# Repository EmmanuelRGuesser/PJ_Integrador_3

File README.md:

---

# Medidor de consumo elétrico residencial com ESP32
---

Este projeto tem como objetivo realizar o projeto e implementação de um dispositivo de monitoramento do consumo energético de tomadas residenciais integrado ao Home Assistant.

Dispositivos como esse permitem aos usuários monitorar e controlar o consumo de energia, ajudando a identificar aparelhos que consomem muita energia e incentivar hábitos mais sustentáveis. Isso resulta em uma redução significativa na fatura de energia e contribui para a conservação de recursos naturais.

Com o aumento das tarifas de energia elétrica, ser capaz de identificar os maiores consumidores de energia em casa pode gerar economia substancial. Um dispositivo que fornece dados detalhados permite aos consumidores tomar decisões informadas para reduzir o consumo e, consequentemente, os custos.

## Funcionalidades:

- Integração com o Home Assistant;
- Monitoramento da tensão, corrente, potência, frequência e fator de potência;
- Visualiazação do histórico de consumo;
- Sistema de acionamento a distância;
- Sistema de proteção do dispositivo.  

## Dispositivo

O dispositivo funcionará entre as tomadas adquirindo os dados por meio do sensor PZEM-004T, abaixo temos uma representação dele:

Ele deve ser conectado a tomada para o fornecimento de energia, dentro da case possui uma fonte para alimentar o ciruito. Esse circuito é composto pelo microcontrolador(ESP32), sensor(PZEM-004t), relé de acionamento e leds para fácil identificação do funcionamento, já a interface será integrada com o Home Assistant.

Para o projeto será utilizado os seguintes componentes:
- ESP32
- PZEM-004t
- Relé
- Fonte Hi-link 5V 3W
- 2 leds
- Display LCD 20x4
- Case takachi WPL15-15-6

---
## Descrição dos componentes

### ESP32
O ESP32 é um microcontrolador de baixo custo e baixa potência, desenvolvido pela Espressif Systems. Ele integra Wi-Fi e Bluetooth, tornando-se uma escolha popular para projetos de Internet das Coisas (IoT), além disso a comunidade em torno do ESP32 é enorme, com muitos recursos, bibliotecas e tutoriais disponíveis. A Espressif, empresa desenvolvedora, também oferece um SDK robusto (ESP-IDF). 

### PZEM-004t
O PZEM-004T é um módulo que possui funcionalidades de Voltimetro, Amperímetro e Wattimetro. Os dados são transmitidos para o microcontrolador por meio de comunicação serial TTL. 

### Fonte Hi-link 5V
É um conversor step down que trabalha com uma tensão de alimentação AC-DC 127/220V para 5V, com uma potencia de 5W, o qual será suficiente para alimentar o microcontrolador e os periféricos contidos no circuito. Foi escolhido esse modelo de fonte pois é compacta, facil de encontrar no mercado e possui certificações que garantem a qualidade da tensão e corrente entregues na saída, dentro da potencia especificada.

### LEDs
O dispositivo conta com dois leds que dão um feedback do funcionamento do sistema. Um led vermelho indicará que o circuito está ligado e outro led verde indicará estado de conexão com o wifi.

---
## Home Assistant

O Home Assistant é uma plataforma de automação residencial de código aberto que permite controlar dispositivos e sistemas em sua casa de maneira centralizada e automatizada. Ele suporta uma ampla variedade de dispositivos e protocolos, facilitando a criação de cenários de automação e controle de tudo, desde luzes e termostatos até câmeras de segurança e sistemas de entretenimento.

#### Principais características do Home Assistant:
- Automação: Criação de regras de automação personalizadas com base em eventos, horários ou condições específicas.
- Integrações: Suporte a milhares de dispositivos e serviços, como Philips Hue, Google Assistant, Amazon Alexa, entre muitos outros.
- Controle Local: Embora possa ser integrado à nuvem, o Home Assistant é projetado para funcionar localmente, o que oferece maior privacidade e controle.
- Dashboard Personalizado: A plataforma oferece uma interface visual personalizável para que você possa monitorar e controlar dispositivos.

#### Integração com ESP32 no Home Assistant
O ESP32 é um microcontrolador com conectividade Wi-Fi e Bluetooth, amplamente utilizado em projetos de automação e IoT (Internet das Coisas). No contexto do Home Assistant, o ESP32 é frequentemente usado para criar dispositivos personalizados, como sensores e atuadores. A integração entre o ESP32 e o Home Assistant ocorre principalmente por meio do protocolo MQTT Moskitto.

Funcionamento da Integração:

1. Configurar a rede Wi-Fi e login do Home Assistant na pagina WEB gerada pelo ESP.
2. O Home Assistant recebe os dados por meio do protocolo MQTT Moskito.
3. Armazena os dados em forma de entidades, no bando de dados InfluxDB.
4. No banco de dados possui um dashboard o qual mostra todos os dados plotados para o gerenciamento.

---

## Funcionamento do Monitor de Energia

Para o funcionamento do dispositivo devemos conectar a rede Wi-FI, isso é feito através do aplicativo ESP BLE Provising que está disponível na Play Store e App Store, leia o [código QR do link](https://espressif.github.io/esp-jumpstart/qrcode.html?data=%7B%22ver%22:%22v1%22,%22name%22:%22Monitor%20de%20energia%22,%22pop%22:%22abcd1234%22,%22transport%22:%22ble%22%7D) ou procure por monitor de energia e use a senha “abc1234”, com isso você pode ver as redes disponíveis e fazer a conexão, caso necessário reconfigurar a rede, somente pressione o botão ao lado da entrada de alimentação por 3 segundos que seu dispositivo irá reiniciar e basta seguir os passos anteriores. 

Agora é possível acessar a página de configurações através do Web Server gerado pela ESP32, acesse [monitor-energia.local](http://monitor-energia.local/), através dela você deve configurar o serviço MQTT para realizar a comunicação de dados entre o monitor de energia e o Home Assistant, use sua conta e senha do seu perfil do HA. Você também pode configurar os alertas, visualizar o consumo acumulado, além de ligar e desligar o dispositivo conectado através da página.

O sistema de alertas funciona como uma proteção que irá atuar desligando o dispositivo conectado ao monitor, a proteção age sobre tensão mínima e tensão, corrente e potência máxima, sempre que um alerta é disparado um aviso é exibido na tela, para voltar ao funcionamento basta clicar no botão ligar. Caso você queira não utilizar os alertas, somente deixe o item com 0. 
Na página de consumo acumulado é exibido quantidade de energia consumida pelo dispositivo conectado, com isso você pode estimar o valor gasto com ele, caso você queira trocar o dispositivo monitorado ou no que for necessário, você pode zerar o contador clicando em zerar energia.

Com isso, já é possível ver na tela LCD do monitor dados como tensão, corrente, potência e energia consumida, além dos avisos do dispositivos e informaçãoes já descritas acima, isso sem a necessidade de integrar com o Home Assistant , porém para conseguir monitorar os dados ao decorrer do tempo em um gráfico, você deve seguir os passos abaixo.

---
### Instalação do Home Assistant
Como o Home Assistant funciona localmente é necessário fazer a instalação em um computador, máquina virtual ou um Raspberry Pi por exemplo. 

Para acessar o processo de instalação [click aqui](https://www.home-assistant.io/installation/).

Com o Home Assistant instalado vamos adicionar o Moskitto MQTT

---
### Guia para Adicionar MQTT Mosquitto no Home Assistant
Instalar o Add-on:

Acesse Configurações → Add-ons, Backup & Supervisor
Vá em Loja de Add-ons e instale o Mosquitto broker
Configurar o Mosquitto:

No add-on, clique em Configuração e edite conforme necessário
Se precisar de autenticação, crie usuários em Configurações → Pessoas e Acesso
Habilitar e Iniciar:

Ative Iniciar na inicialização e Assistente de Rede
Clique em Iniciar
Verificar Funcionamento:

Vá em Configurações → Dispositivos e Serviços
Adicione uma integração MQTT, com isso no menu de configurações já deve ser possível se inscrever em algum tópico para receber os pacotes via MQTT.
No momento têm-se o tópico *sensor* e os sub tópicos *voltage, current, power, energy, frequency e pf*, para ver a tensão por exemplo, deve-se se inscrever no *sensor/voltage*, como resultado você deve ver algumo semelhante a isto:

Para salvar os dados será utilizado o File editor para criar as entidades que serão atribuidas aos dados que são recebidos via mqtt.

Com o File Editor aditaremos o arquivo */homeassistant/configuration.yaml*, basta adicionar o seguinte código para criar as entidades:
```
mqtt:    
    sensor:
        - name: voltage
          state_topic: "sensor/voltage"
          unit_of_measurement: V

        - name: current
          state_topic: "sensor/current"
          unit_of_measurement: A

        - name: power
          state_topic: "sensor/power"
          unit_of_measurement: W

        - name: energy
          state_topic: "sensor/energy"
          unit_of_measurement: Wh

        - name: frequency
          state_topic: "sensor/frequency"
          unit_of_measurement: Hz
          
        - name: fp
          state_topic: "sensor/pf"
          unit_of_measurement: fp
```
Agora vamos criar o banco de dados com o InfluxDB, para armazenar os dados e os manipular.

---
### Adicionando o InfluxDB no Home Assistant
Instalar o Add-on:

Acesse Configurações → Add-ons, Backup & Supervisor
Instale o InfluxDB
Criar um Banco de Dados e Usuário:

No terminal do InfluxDB, execute:
```
CREATE DATABASE home_assistant;
CREATE USER ha_user WITH PASSWORD 'senha' WITH ALL PRIVILEGES;
```
(Opcional) Restringir permissões:
```
GRANT ALL ON home_assistant TO ha_user;
```
Configurar no Home Assistant:
Adicione no configuration.yaml:
```
influxdb:
  host: a0d7b954-influxdb
  port: 8086
  database: home_assistant
  username: ha_user
  password: senha
  max_retries: 3
  default_measurement: state
```
Reinicie o Home Assistant

Para Verificar Funcionamento:

Acesse Desenvolvedor → Ferramentas de Estado para ver os dados sendo enviados

Pronto! Agora o MQTT e o InfluxDB estão integrados ao Home Assistant. 🚀

---
### Gerar o Dashboard e os gráficos no InfluxDB
1. Acessar o InfluxDB
2. No Home Assistant, vá para Configurações → Add-ons, Backup & Supervisor
Abra o InfluxDB e clique em Abrir Web UI
3. Criar um Dashboard
No menu lateral, vá em Dashboards
Clique em + Create Dashboard
Dê um nome ao dashboard e clique em Create
4. Criar um Gráfico
No dashboard criado, clique em + Create Cell
Escolha o tipo de visualização (Linha, Barras, Gauge, etc.)
Selecione Configure Query e escolha o banco de dados home_assistant
5. Construir a Query
   
OBS: O código das query estão no arquivo [Código_dos_gráficos_influxDB.md](https://github.com/EmmanuelRGuesser/PJ_Integrador_3/blob/main/C%C3%B3digo_dos_gr%C3%A1ficos_influxDB.md)

6. Utilizando os códigos, você pode personalizar os gráficos como desejar.

---

### Teste do Monitor de Energia

Para o teste vamos monitorar o carregamento de um notebook, após realizar as configuração de conexão do monitor e do Home Assistant conforme o passo a passo acima, podemos monitorar o consumo através da tela LCD no monitor ou pelo dashboard no Home Assistant.

Como visto acima podemos monitorar os parâmetros elétricos do dispositivo conectado ao monitor. Vamos testar o sistema de proteção, como a potência consumida é entre 15W - 20 W então para provocar um alerta iremos limitar em 10W, para isso entramos no página web do monitor de energia → configurar alertas e colocamos Max Power com 10W.

Como vemos acima o monitor entra em modo proteção e desliga a carga, para voltar a funcionar é necessário ligar novamente no menu principal.

O consumo acumulado pode ser acessado pelo menu e la você poderá estimar o valor gasto pela caraga conectada, somente digite o valor pago por kWh e calcule. Caso você quiser zerar o contador nesta página também é possível fazer isto.

---

## Considerações finais

O desenvolvimento do projeto atingiu seus objetivos propostos, resultando em um dispositivo funcional capaz de monitorar o consumo elétrico de forma eficiente. A integração do hardware e software permitiu a coleta e visualização dos dados em tempo real, proporcionando um produto prático para automação residencial. Para projetos futuros, considera-se a possibilidade de utilizar um banco de dados mais robusto, um software mais avançado para a criação do dashboard e a adoção de componentes SMD para um design mais compacto, eficiente e profissional, reduzindo o tamanho da case e aprimorando a estética e usabilidade do dispositivo.

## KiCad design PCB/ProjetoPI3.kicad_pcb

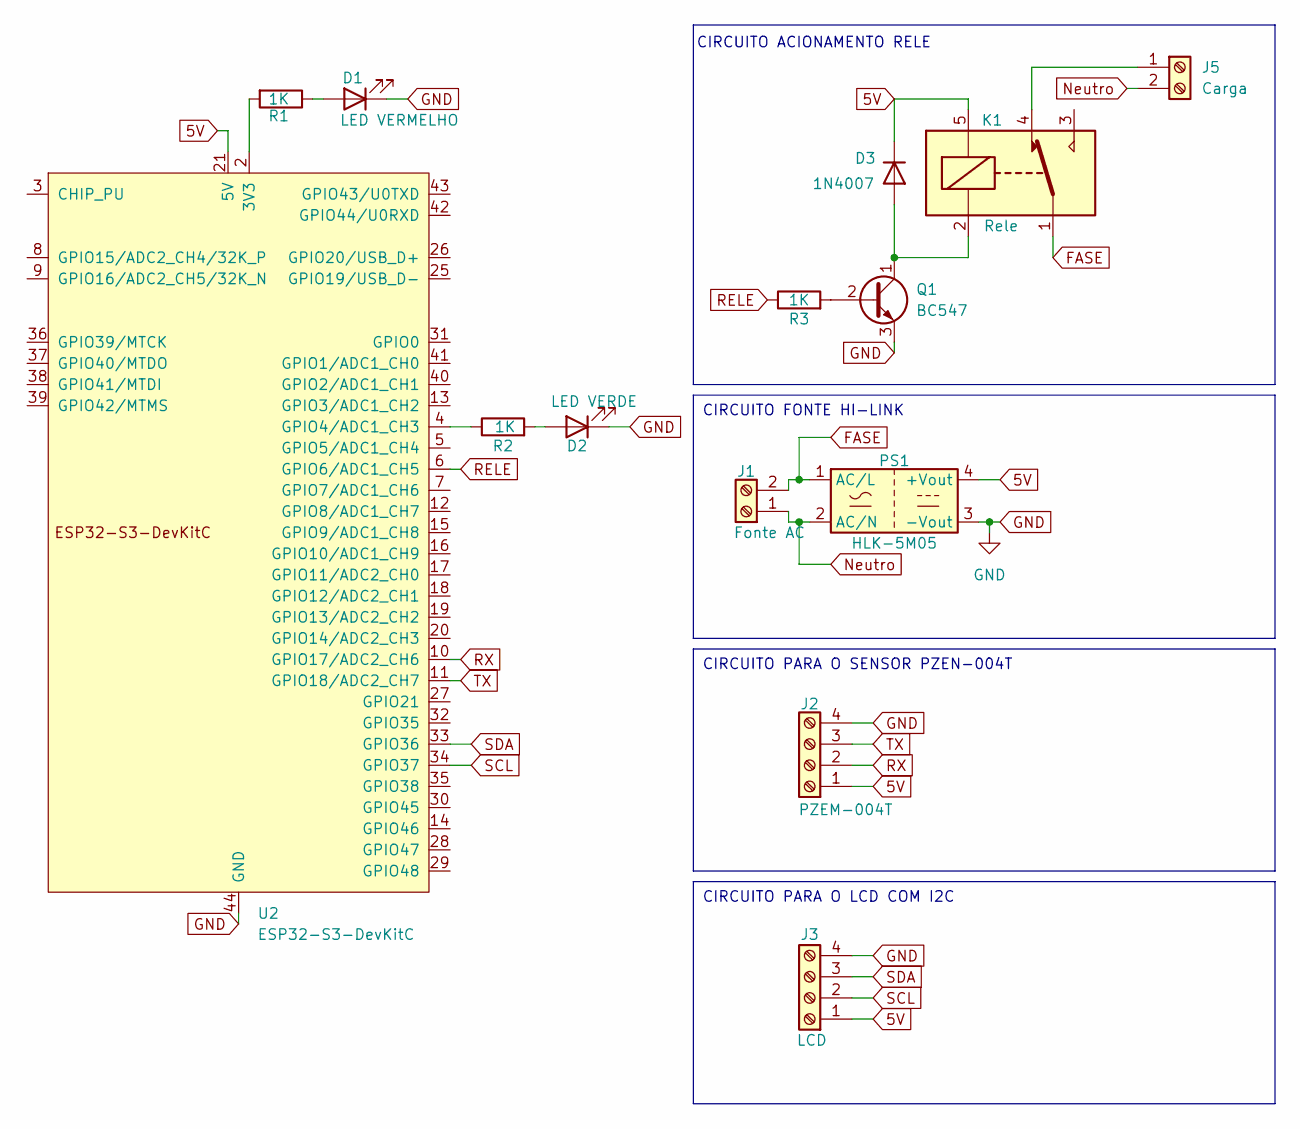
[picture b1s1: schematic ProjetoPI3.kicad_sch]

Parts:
D1: LED VERMELHO; TerminalBlock_Altech_AK300-2_P5.00mm
D2: LED VERDE; TerminalBlock_Altech_AK300-2_P5.00mm
D3: 1N4007; D_DO-41_SOD81_P10.16mm_Horizontal
J1: Fonte AC; TerminalBlock_Altech_AK300-2_P5.00mm
J2: PZEM-004T; TerminalBlock_Altech_AK300-4_P5.00mm
J3: LCD; TerminalBlock_Altech_AK300-4_P5.00mm
J5: Carga; TerminalBlock_Altech_AK300-2_P5.00mm
K1: Rele; Relay_SPDT_SANYOU_SRD_Series_Form_C
PS1: HLK-5M05; Converter_ACDC_Hi-Link_HLK-5Mxx
Q1: BC547; TO-92_Inline
R1, R2, R3: 1K; R_Axial_DIN0207_L6.3mm_D2.5mm_P10.16mm_Horizontal
U2: ESP32-S3-DevKitC

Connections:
5V: D3.1 (K), J2.1, J3.1, K1.5, PS1.4 (+Vout), U2.21 (5V)
FASE: J1.2, K1.1, PS1.1 (AC/L)
GND: D1.1 (K), D2.1 (K), J2.4, J3.4, PS1.3 (-Vout), Q1.3 (E), U2.22 (GND), U2.23 (GND), U2.24 (GND), U2.44 (GND)
unnamed: D1.2 (A), R1.1
unnamed: D2.2 (A), R2.2
unnamed: D3.2 (A), K1.2, Q1.1 (C)
unnamed: J5.1, K1.4
unnamed: Q1.2 (B), R3.2
unnamed: R1.2, U2.1 (3V3), U2.2 (3V3)
unnamed: R2.1, U2.4 (GPIO4/ADC1_CH3)
Neutro: J1.1, J5.2, PS1.2 (AC/N)
RELE: R3.1, U2.6 (GPIO6/ADC1_CH5)
RX: J2.2, U2.10 (GPIO17/ADC2_CH6)
SCL: J3.2, U2.34 (GPIO37)
SDA: J3.3, U2.33 (GPIO36)
TX: J2.3, U2.11 (GPIO18/ADC2_CH7)

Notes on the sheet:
CIRCUITO PARA O SENSOR PZEN-004T
CIRCUITO FONTE HI-LINK
CIRCUITO PARA O LCD COM I2C
CIRCUITO ACIONAMENTO RELE

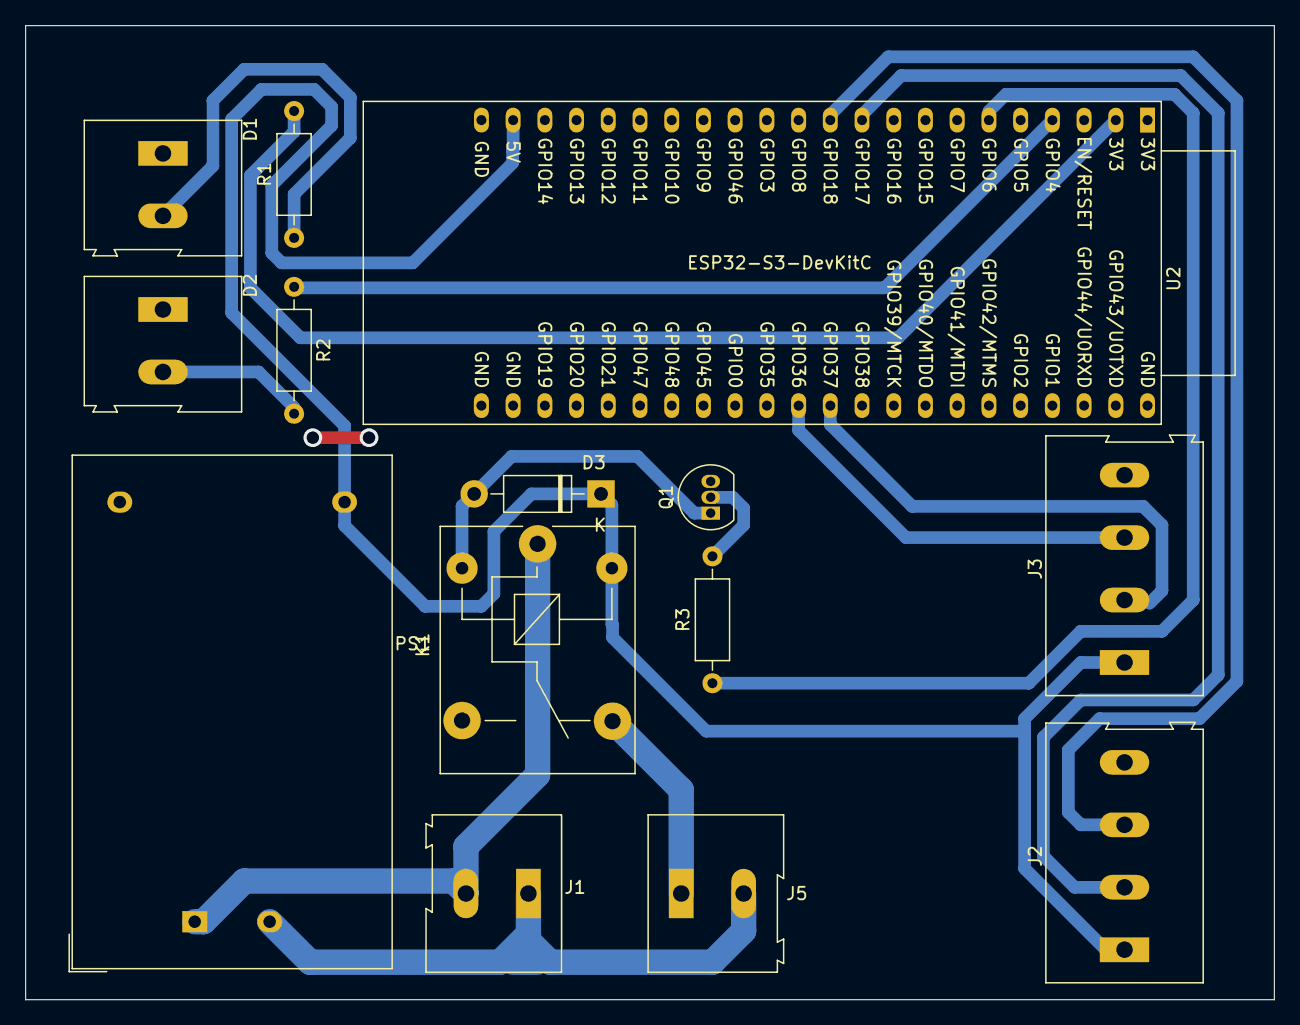
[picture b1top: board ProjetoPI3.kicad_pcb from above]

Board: 2 copper layers, 100.0 x 78.0 mm, 14 parts (0 on the bottom side), 16 nets.

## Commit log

2024-10-22 Update README.md
    descrições iniciais V1.0
2024-10-23 Adicionado imagens do projeto
2024-10-23 Update README.md
    atualização na descrição da fonte hi-link e do sensor PZEM-004T
2024-11-04 Create FonteTeste
    Testes realizados com a fonte Hilink
2024-11-04 Update and rename FonteTeste to FonteTeste.md
    Finalizado arquivo de testes fonte
2024-11-06 Add files
2024-11-06 Add imgs
2024-12-02 Create ProjetoPlacaKicad.md
    Arquivo contendo explicações referentes ao projeto da placa.
2024-12-04 Add imagens de exemplo
2024-12-04 Ajuste nas mensagens mqtt
2025-01-14 Add LCD Monitor
2025-02-09 Atualizações e adição de funcionalidades.
    Adicionado WebServer, atualizações no provisionamento WiFi e MQTT e correções no display.
2025-02-09 Add mDNS component
2025-02-11 Update ProjetoPlacaKicad.md
    alterações textuais
2025-02-11 Contém os códigos referente aos gráficos do dashboard
2025-02-11 Update README.md
    Atualização textual do readme
2025-02-12 Add imagens
2025-02-12 Adicionado imagens
2025-02-12 Add PCB
